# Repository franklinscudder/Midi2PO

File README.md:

# Midi2PO
 A device that takes MIDI clock in and outputs 1v pulses at PPQN intervals compatible with a range of devices including Korg volcas and Teenage Engineering pocket operators.

## V1
An initial design outputting a 2PPQN signal for PO/Volcas.

## V2 (LC)
An untested lower cost design using a ATTiny uController.

## V3 (Switchable)
An iteration including a second LED indicator as well as a DIP switch bank to allow a range of PPQN values to be output.
Available PPQNS: 0.25, 0.5, 1, 2, 4, 6, 12, 24.

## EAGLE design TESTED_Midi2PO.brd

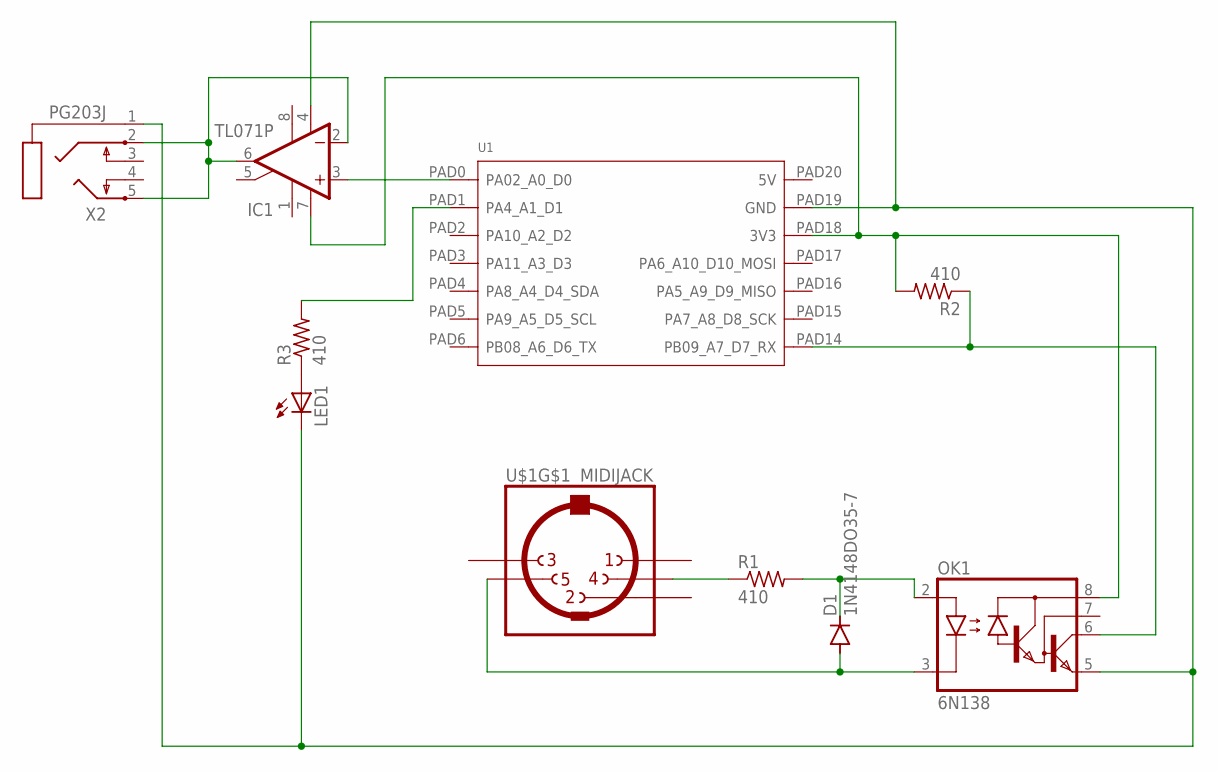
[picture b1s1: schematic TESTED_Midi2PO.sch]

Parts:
D1: 1N4148DO35-7; DO35-7
IC1: TL071P; DIL08
LED1: LED5MM
OK1: 6N138; DIL08
R1, R2, R3: 410; 0207/9
U1: MOUDLE-SEEEDUINO-XIAO; MOUDLE14P-2.54-21X17.8MM
U$1: MIDIJACK; CP-2350
X2: PG203J

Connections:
unnamed: D1.C, OK1.2 (A), R1.2
unnamed: R1.1, U$1.4
unnamed: D1.A, OK1.3 (C), U$1.5
unnamed 3: IC1.4 (V-), LED1.K (C), OK1.5 (GND), U1.PAD19 (GND), X2.1; also elsewhere on the board
unnamed: OK1.6 (VO), R2.1, U1.PAD14 (PB09_A7_D7_RX)
unnamed: IC1.7 (V+), OK1.8 (VCC), R2.2, U1.PAD18 (3V3)
unnamed: IC1.3 (+IN), U1.PAD0 (PA02_A0_D0)
unnamed: LED1.A, R3.1
unnamed: R3.2, U1.PAD1 (PA4_A1_D1)
unnamed 9: IC1.2 (-IN), IC1.6 (OUT), X2.2, X2.5; also elsewhere on the board

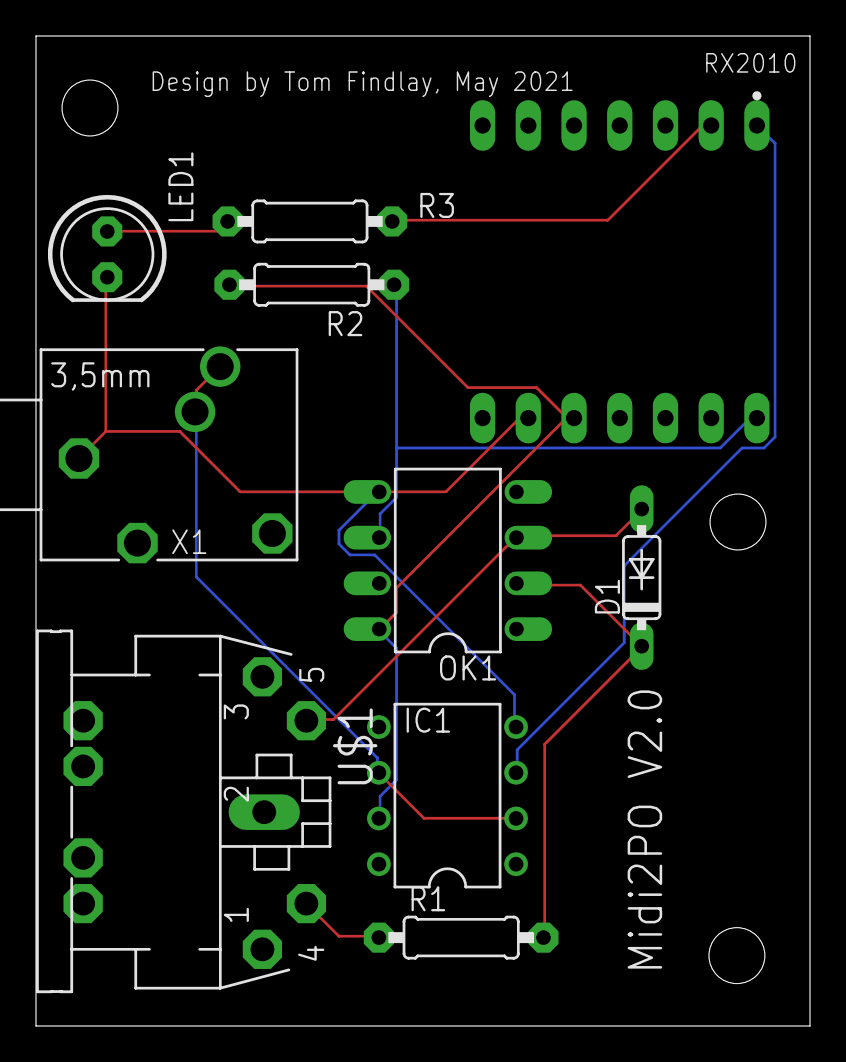
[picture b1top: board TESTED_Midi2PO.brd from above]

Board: 2 copper layers, 43.0 x 55.0 mm, 10 parts (0 on the bottom side), 10 nets.

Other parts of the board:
X1: 1503_09; PG203J

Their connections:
unnamed 3: X1.1; also elsewhere on the board
unnamed 9: X1.2, X1.3; also elsewhere on the board

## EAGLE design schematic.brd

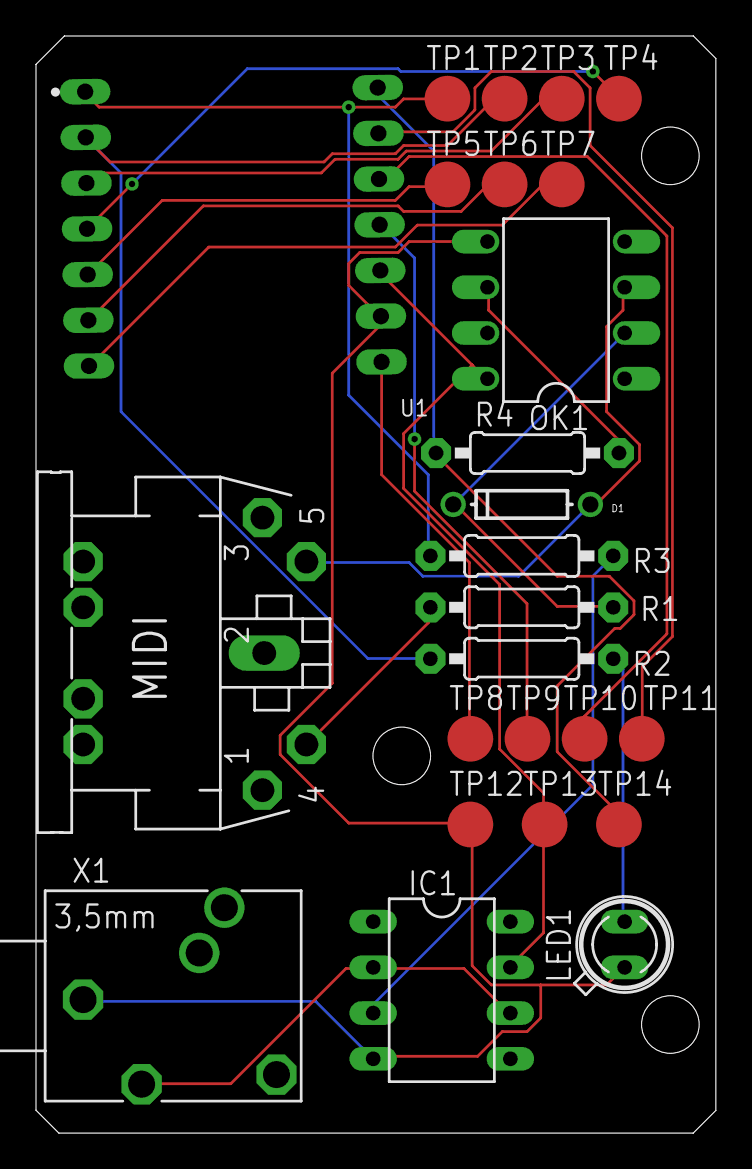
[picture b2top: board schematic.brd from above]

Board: 2 copper layers, 37.8 x 60.9 mm, 25 parts (0 on the bottom side), 21 nets.

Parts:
D1: DO-1N4148
IC1: TL071P; DIL08
LED1: SFH480
MIDI: MIDIJACK; CP-2350
OK1: 6N138; DIL08
R1: 220; 0207/10
R2: 100; 0207/10
R3: 1k; 0207/10
R4: 270; 0207/10
TP1, TP2, TP3, TP4, TP5, TP6, TP7, TP8, TP9, TP10, TP11, TP12, TP13, TP14: TPB2,54; B2,54
U1: MOUDLE14P-2.54-21X17.8MM
X1: PG203J

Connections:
unnamed: D1.C, OK1.2, R1.2
unnamed: MIDI.4, R1.1
unnamed: D1.A, MIDI.5, OK1.3
unnamed: TP3.TP, U1.PAD2
unnamed: IC1.7, OK1.8, TP13.TP, U1.PAD18
unnamed: R4.1, TP14.TP, U1.PAD14
unnamed: TP4.TP, U1.PAD3
unnamed: R3.2, TP1.TP, U1.PAD0
unnamed: TP5.TP, U1.PAD4
unnamed: IC1.3, R3.1
unnamed: IC1.2, IC1.6, X1.5
unnamed: TP6.TP, U1.PAD5
unnamed: TP7.TP, U1.PAD6
unnamed: LED1.A, R2.1
unnamed: IC1.4, LED1.K, OK1.5, TP12.TP, U1.PAD19, X1.1
unnamed: R2.2, TP2.TP, U1.PAD1
unnamed: TP8.TP, U1.PAD20
unnamed: TP9.TP, U1.PAD17
unnamed: TP10.TP, U1.PAD16
unnamed: TP11.TP, U1.PAD15
unnamed: OK1.6, R4.2

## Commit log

2021-05-26 Restructured Project
